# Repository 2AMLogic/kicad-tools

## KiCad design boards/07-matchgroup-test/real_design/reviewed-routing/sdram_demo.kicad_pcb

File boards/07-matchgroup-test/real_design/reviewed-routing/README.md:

# Reviewed physical routing

`sdram_demo.kicad_pcb` is the explicit routing/length-tuning artifact for the
43-part, 216-binding real SDRAM circuit. `manifest.json` binds its SHA-256 and
the exact authored source manifest. It includes the completed copper and
operator silkscreen; it is not a generic autorouter cache entry.

Run `../build.py OUTPUT` through `uv run python` to regenerate the independent
electrical source and repeat every design gate. A new logical circuit, physical
package placement or source-rule manifest requires a new reviewed routing
artifact and fresh validation; updating a hash alone is not a design review.

The build intentionally distinguishes design validation from manufacturing
export. The final order package must be generated afterward and its manifest
must pass before manufacturing readiness is claimed. Hardware has not yet been
tested.

## Class-clearance repair (Issue #6396)

The reviewed copper was first validated against the 0.15 mm native floor only.
Once #6390 declared the board's own 0.175 mm `AUX`/`SDRAM_*` classes, 42
track-to-via/pad gaps fell 0.2–25 µm short. `../repair_class_clearance_6396.py`
is the complete record of the fix. It moves 24 vias by 10–47 µm, re-attaches
their stubs at 0/45/90°, and moves one GND escape by 7 µm, then re-pins both
manifests. No class value changed. Run it with `--verify-from-git 810f833f` to
reproduce both committed PCBs byte for byte from the pre-repair artifacts.

## Evidence refresh (Issue #6404)

`build.py` fills the planes under the published router net classes, the same
`.kicad_pro`/`.kicad_dru` that sit beside the routed board. Before this, the
fills used the fab floor alone, and the saved fills failed native DRC without
`--refill-zones`. The files under `evidence/` come from that build of the
repaired copper. `scripts/boards/refresh_bundles_6404.py` regenerates them,
the routed board's fills and the manufacturing bundle together.

## Same-net copper-gap repair (Issue #9091)

Once #8938 graded same-net `physical_copper_gap` findings as errors, the
reviewed copper had 25 same-net slits: nine vias 0.07–0.12 mm from their own
pads, and narrow same-net wedges at U2.50 (DQ13), U2.39 (UDQM) and U2.53
(DQ15). `../repair_copper_gap_9091.py` is the complete record of the fix.
- It moves the nine vias 53–87 µm clear of their pads.
- It replaces a +5V staircase beside C26 with a plain T, which frees one of
  those vias.
- At DQ13 and UDQM, it removes the loops. Each trunk ran through its own pad
  and doubled back along the pad's escape, so the loop counted about 10 mm of
  length the signal never travelled. The script restores that length with
  `SerpentineGenerator` trombones on the trunks.
- It turns DQ15's shallow staircase join into a right angle and puts the
  1.5 mm it removes back into DQ15's existing meander.

Every `SDRAM_BYTE1` length is unchanged to 1 µm. DQ7 gains 0.145 mm. Run the
script with `--verify-from-git 89c2ee058` to reproduce both PCBs byte for byte.

The files under `evidence/` now describe the adopted #8603 copper (see the
section below); `refill-stability.json` and the published `../../output/`
release still describe the copper as it was before the November 2026 prune
(95c4c7eaf), until #8604's evidence refresh re-issues them.

## SDRAM_BYTE0 same-net loops (Issue #9118)

DQ7 (U2.13) and LDQM (U1.141) had the byte-1 defect from #9091: each trunk ran
through its own pad and on past it, and the authored escape doubled back along
the trunk. That is 6–7 mm of copper per net the signal never travels, but
`validate.py` sums it as matched length. Measured as the shortest path through
the copper, the real byte-0 spread was 7.51 mm against `group_skew_mm` 5.0 as
filed (the board-local model #9118 was filed with; removed by #9176). The
shared contact model, `TraceLengthAnalyzer.measure_net_path`, reads 8.16 mm on
the same stripped copper. `../repair_byte0_loops_9118.py` is the complete
record of the fix.
- It removes the loop copper, so each trunk ends inside its own pad.
- It restores the length as real series length: two `SerpentineGenerator`
  trombones, 5.93 mm on DQ7 and 6.98 mm on LDQM, on free F.Cu.
- It changes no tolerance and not `authored-source`, which never held the loops
  in this form. Only this directory's manifest is re-pinned.

Physical byte-0 spread is now 1.18 mm through `TraceLengthAnalyzer
.measure_net_path` (canonical since #9176: DQ5 62.20 to DQ2 63.37 mm; the
removed board-local model read 0.92 mm). Run the script with
`--verify-from-git c694302cd` to reproduce the PCB byte for byte, and print
the per-net lengths by measuring each with `measure_net_path` the way
`tests/test_board07_byte0_physical_spread.py` pins them.

`build.py` still reaches the same end state as after #9091: 0 native DRC
violations, 0 unconnected items, clean label and copper LVS, and only its full
`kct check` gate failing on `mask_to_copper` (#8858). `../../output/` is
therefore not re-issued here.

## Six-layer warning-free re-issue (Issue #8603)

After the November 2026 prune the reviewed copper still failed the full
`kct check` gate with 210 warnings (163 `redundant_copper_fragments`, 30
covered tracks, 14 detours and 3 silk findings), all traced to 0.05 mm
optimizer staircases that `kct pcb prune` cannot collapse. The #8603
operator ruling (option 2, 2026-11-10) authorized re-optimizing the
reviewed copper instead of accepting them.

`../engineering/retune_8603.py` optimizes the release build against the
board's own generated `.kicad_pro`/`.kicad_dru` (JLCPCB six-layer profile),
retunes the four match groups and re-derives the 14 pad-to-via authored
escapes. `../engineering/cleanup_8603.py` then simplifies the remaining
sub-0.1 mm fragment runs between their original terminals, removes covered
tracks, adds 21 same-net layer-handoff vias and stages the assembly
artwork. Both scripts refuse any input whose SHA-256 differs from the
recorded digest, and the recipe reproduces both committed PCBs byte for
byte from Git inputs:

```sh
KCT_KICAD_DOCKER=1 uv run python boards/07-matchgroup-test/real_design/engineering/cleanup_8603.py OUT
```

`sdram_demo.kicad_pcb` here is
`45943c244519945ee5d51c4b58a28a901cf67b092129c64dcd2ea90a11d2bc84` and the
authored source is
`ebff1f52709d4cb1a56d6b1558ca1051c223b746c37825ecd93c38ea81bc7575`
(`reviewed_on` 2026-11-22; the authored manifest also declares the six
board-only fiducial marks that `../build.py` and `../build_source.py` now
verify). The full gate this build repeats reports 0 errors and 0 warnings:
every `redundant_copper_*` class is 0, native DRC and ERC report no
violations, both LVS checks bind all 216 pads, the byte-0 / byte-1 /
address / command spreads are 1.952 / 4.605 / 3.648 / 4.027 mm against the
5.0 mm limit, the largest clock-relative difference is 9.881 mm and the
smallest non-pad clock gap is 0.560 mm against the 0.54 mm screen.

The redundant-copper census above runs
on the validated artifact with the board's generated `.kicad_pro` net
classes beside it. Checking the raw committed file without that project
context instead flags five candidate staircases (BOOT0, DQ1 and three
more) whose one-bend shortcuts would violate the 0.175 mm class
clearances, so the gate context is the authoritative one.

## Manufacturing recheck (Issue #8604)

The independent review on 2026-11-22 repeated the build and validator from
the post-merge inputs. Both SHA-256 values above still match the reviewed and
authored PCBs. The saved, filled production PCB is
`716d270e82df33950d7bc65c27aecc02cd4932ca9c6112429361a13db21791fb`.
Two independent builds produced this digest. At the first refill, KiCad
adds two hidden fabrication fields to each fiducial. The validator retains
all 2,869 reviewed identifiers and assigns reproducible identifiers to
those 12 fields before repeating the native save.
Pinned KiCad 10.0.6 found zero violations and opens on the saved copper and
after a separate refill. Both LVS checks bound all 216 pads. The 38 timed
nets passed their group, clock-relative and load limits. See the
[group measurements](../README.md) and [clock spacing](evidence/clock-spacing.json).

The order package uses the same filled PCB and the production DRU for both
plots and checks. Its assembly CSV contains all 43 placements. The six
board-only fiducials are present in the fabrication artwork. Hardware
testing remains pending.

## Reviewed class widths (Issue #10451)

`kct check`'s `netclass_agreement` rule (#10139) landed after this evidence
was pinned. It compares each routed net's sidecar class and `trace_width`
with the class the sibling project resolves for that net. On this board it
reported 55 `netclass_sidecar_mismatch` warnings: the six router classes in
the routed project inherited the 0.160 mm `track_width` of `Default`
(`apply_router_netclasses` clones `Default` and overrides only the name and
clearance), while `net_class_map.json` declared 0.180 mm for the 39 SDRAM
and `SWD_CLOCK` nets and 0.200 mm for the 16 `AUX` nets. `build.py` requires
zero warnings, so the replay stopped at its own design gate (#10447).

The reviewed widths are now declared in the maintained source, where they
resolve before the first zone fill. `authored-source/sdram_demo.kicad_pro`
gives `Default` the reviewed 0.180 mm that every declared class inherits, and
`authored-source/net_class_map.json` declares `AUX` at 0.180 mm. No copper
changed.

**AUX width, 0.180 mm.** The class holds the sixteen non-SDRAM nets: the
`+5V`, `+3V3` and `+3V3_A` supplies, `GND`, the `VCAP1`/`VCAP2` capacitor
links, reset, boot, debug, UART and the LED nets. On the reviewed routing,
229 of 252 `AUX` segments are 0.180 mm. That includes every supply and ground
segment and is the width the authored power routing and package escapes
carry. The other 23 segments, on `BOOT0`, `NRST`, `SWO`, `UART_TX`,
`UART_RX`, `LED_PASS_A` and `LED_FAIL_A`, are 0.200 mm. The class width is a
minimum, so those stay legal. No `AUX` net is impedance-controlled or
length-matched. IPC-2221 screening with the board's own stackup
(`kicad_tools.physics.ampacity`) needs 0.040 mm for the 230 mA bench
envelope on the 35 µm outer copper, where a 0.180 mm track screens near
0.69 A at a 10 °C rise; the inner-layer `AUX` copper carries only the
filtered analog supply and signal currents. Declaring 0.200 mm would have
reported the 229 reviewed segments as narrow and required re-routing supply
and ground to satisfy a width the copper never carried.

**Pad escapes.** No pad escape narrows below its class. Every reviewed
escape carries its class width, none of the 55 sidecar entries declares a
`neck_trace_width`, and the rule's track-width arm reports nothing on this
copper. A trunk segment narrowed below its class does fail it, and
`tests/test_board07_real_design.py` checks both.

**The two writes.** `validate.py` writes the rules once before the first
zone fill (`write_reviewed_rules`) and `kct check --emit-drc-constraints`
writes them again after the copper measurements. `class_width_errors`
resolves the written project against the sidecar after the first write and
names each drifting net before any native step runs. The validator still
requires both native sidecars to be byte-identical across the second.

**Published files.** `output/matchgroup_test_routed.kicad_pro` is the
authored project with `write_reviewed_rules` applied to the published routed
PCB. It is byte-identical to what `build.py` checks and publishes:
`50360572adf6d64ea127da337dccb79a0c9758a428070fa6c69ab73698e6c44c`.
`declare_router_netclasses_6390.py` alone re-declares the classes on
whatever `Default` width the old routed project carried, so it does not
refresh this file. The routed `.kicad_dru`
(`51c411e4dbbb48d70364da6ada60a327b4c61ad718c503b5db7503836919d2b3`) and
the saved, filled routed PCB
(`716d270e82df33950d7bc65c27aecc02cd4932ca9c6112429361a13db21791fb`) are
unchanged. The re-pinned source digests are `net_class_map.json`
`a362225403d2962e7da424ab289a285ac62d417538f4ed05167f9c55e12c224f` and
`sdram_demo.kicad_pro`
`b912b224a3f36a5ff763a9f61f79581572294f1b980bab036d2b6740af51886c`; both
PCBs above are unchanged.

The regenerated schematic carries the instance `Datasheet` the generator
now writes from each symbol definition instead of `~` (#10385); all 46
placed instances changed. `output/matchgroup_test.kicad_sch` and
`output/readiness/checked.kicad_sch` are byte-identical:
`802a7c20582e120f30878c6ae2f1f119243eaa60158da64f1bddbf544204b185`.

**Re-pin.** `scripts/boards/refresh_bundles_6404.py` rebuilt the design from
a fresh build directory and republished the evidence on the pinned
toolchain: `kicad-cli` 10.0.6 through CI's image, the synced 3D model subset
for the renders. The full `kct check` reports 0 errors and 0 warnings, the
saved and the refilled fills are byte-identical with 0 native violations and
0 unconnected items, label and copper LVS are clean, and the receipt is
`ready`. A repeat publish and a dry run from another fresh build directory,
each with the receipt's own timestamp, list 0 files.

**Package.** The re-pinned `cpl_jlcpcb.csv` differs from the previous package
in one cell: `U3` (`AP2112K-3.3TRG1`, LCSC C51118) now exports at 270°, the
catalog correction the shipped JLCPCB table gives that part on SOT-23-5
(issue #10198). The committed CPL predated it at the 180° SOT-23 default.
The bundle driver accepts only coordinate-frame changes from a fresh export,
so the corrected row was written into the committed CPL before the re-pin
and `kct export` then reproduced it byte for byte. No placement moved.

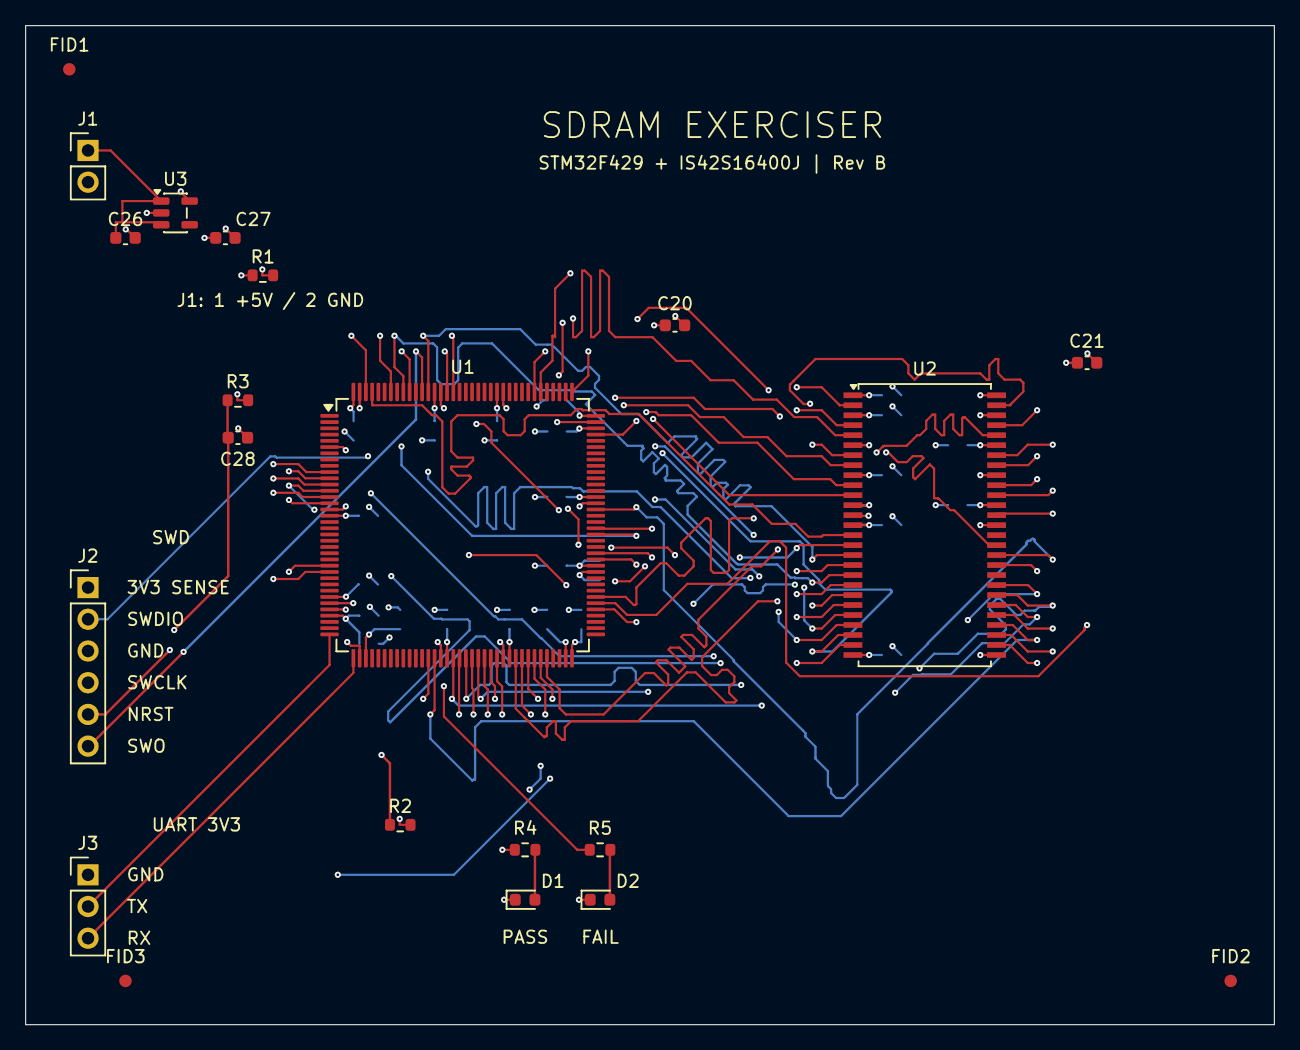
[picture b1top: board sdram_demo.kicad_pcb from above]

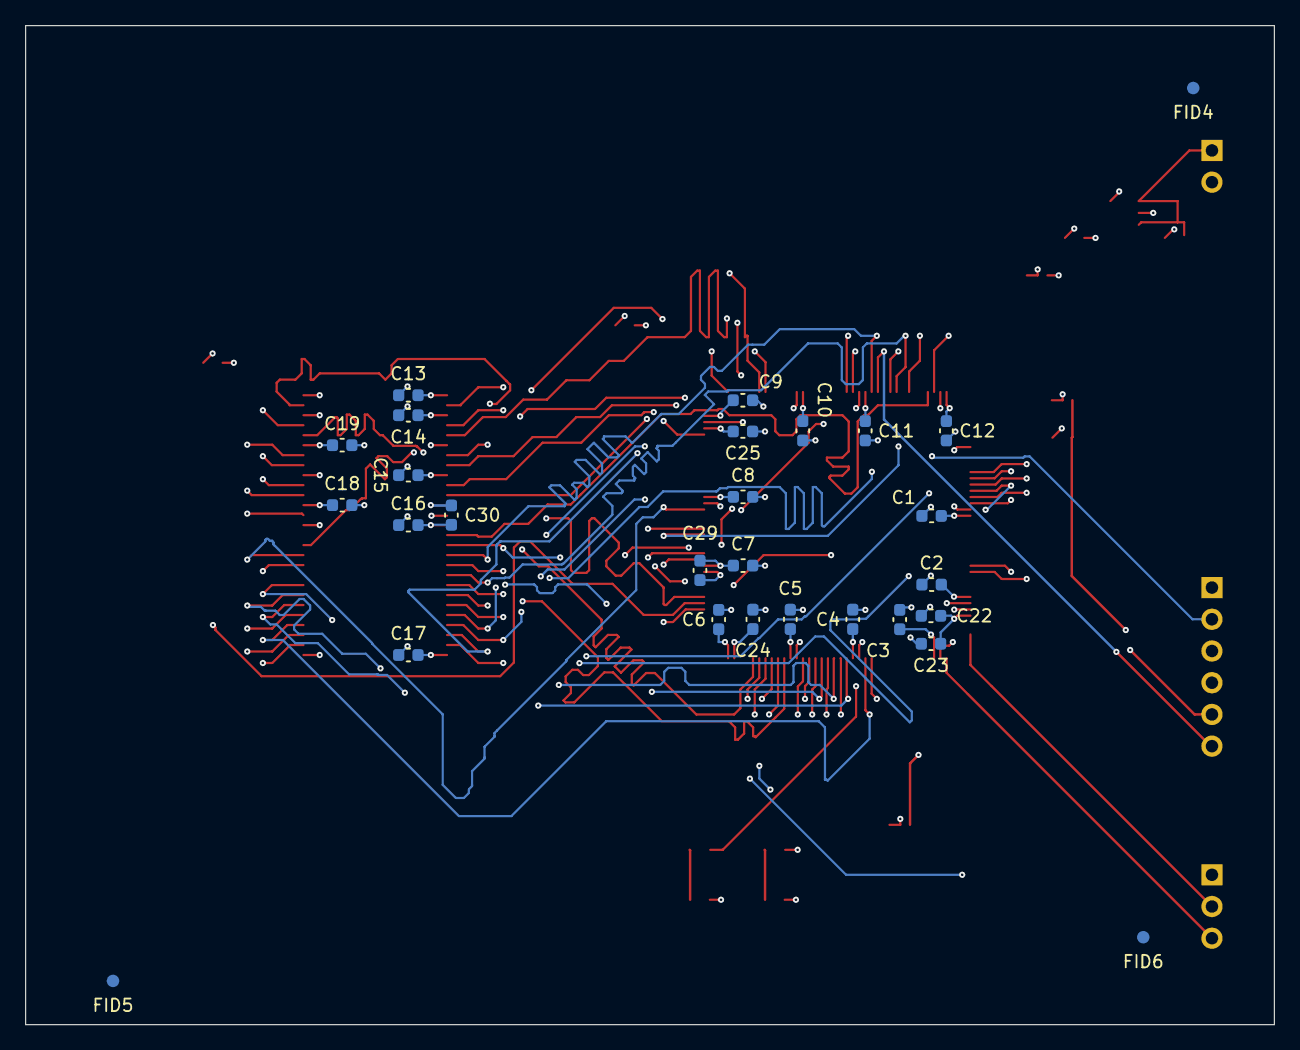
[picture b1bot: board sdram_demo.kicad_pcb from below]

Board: 6 copper layers, 100.0 x 80.0 mm, 49 parts (28 on the bottom side), 55 nets.

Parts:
C1, C2, C3, C4, C5, C6, C7, C8, C9, C10, C11, C12, C13, C14, C15, C16, C17, C18, C19, C22, C28: 100nF; C_0603_1608Metric
C20, C21: 4.7uF; C_0603_1608Metric
C23: 1uF; C_0603_1608Metric
C24, C25: 2.2uF; C_0603_1608Metric
C26, C27: 10uF; C_0603_1608Metric
C29, C30: 10nF; C_0603_1608Metric
D1: GREEN; LED_0603_1608Metric
D2: RED; LED_0603_1608Metric
FID1, FID2, FID3, FID4, FID5, FID6: Fiducial; Fiducial_1mm_Mask2mm
J1: 5V_INPUT; PinHeader_1x02_P2.54mm_Vertical
J2: SWD_3V3; PinHeader_1x06_P2.54mm_Vertical
J3: UART_3V3; PinHeader_1x03_P2.54mm_Vertical
R1: 0R; R_0603_1608Metric
R2, R3: 10k; R_0603_1608Metric
R4, R5: 1k; R_0603_1608Metric
U1: STM32F429ZIT6; LQFP-144_20x20mm_P0.5mm
U2: IS42S16400J-6TLI-TR; TSOP-II-54_22.2x10.16mm_P0.8mm
U3: AP2112K-3.3TRG1; SOT-23-5

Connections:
+3V3: C1.1, C2.1, C3.1, C4.1, C5.1, C6.1, C7.1, C8.1, C9.1, C10.1, C11.1, C12.1, C13.1, C14.1, C15.1, C16.1, C17.1, C18.1, C19.1, C20.1, C21.1, C27.1, C29.1, C30.1, J2.1, R1.1, R3.2, U1.6 (VBAT), U1.17 (VDD), U1.30 (VDD), U1.39 (VDD), U1.52 (VDD), U1.62 (VDD), U1.72 (VDD), U1.84 (VDD), U1.95 (VDD), U1.108 (VDD), U1.121 (VDD), U1.131 (VDD), U1.143 (PDR_ON), U1.144 (VDD), U2.1 (VDD), U2.3 (VDDQ), U2.9 (VDDQ), U2.14 (VDD), U2.27 (VDD), U2.43 (VDDQ), U2.49 (VDDQ), U3.5 (VOUT)
+3V3_A: C22.1, C23.1, R1.2, U1.32 (VREF+), U1.33 (VDDA)
+5V: C26.1, J1.1, U3.1 (VIN), U3.3 (EN)
A0: U1.10 (PF0), U2.23 (A0)
A1: U1.11 (PF1), U2.24 (A1)
A2: U1.12 (PF2), U2.25 (A2)
A3: U1.13 (PF3), U2.26 (A3)
A4: U1.14 (PF4), U2.29 (A4)
A5: U1.15 (PF5), U2.30 (A5)
A6: U1.50 (PF12), U2.31 (A6)
A7: U1.53 (PF13), U2.32 (A7)
A8: U1.54 (PF14), U2.33 (A8)
A9: U1.55 (PF15), U2.34 (A9)
A10: U1.56 (PG0), U2.22 (A10)
A11: U1.57 (PG1), U2.35 (A11)
BA0: U1.89 (PG4), U2.20 (BA0)
BA1: U1.90 (PG5), U2.21 (BA1)
BOOT0: R2.1, U1.138 (BOOT0)
DQ0: U1.85 (PD14), U2.2 (DQ0)
DQ1: U1.86 (PD15), U2.4 (DQ1)
DQ2: U1.114 (PD0), U2.5 (DQ2)
DQ3: U1.115 (PD1), U2.7 (DQ3)
DQ4: U1.58 (PE7), U2.8 (DQ4)
DQ5: U1.59 (PE8), U2.10 (DQ5)
DQ6: U1.60 (PE9), U2.11 (DQ6)
DQ7: U1.63 (PE10), U2.13 (DQ7)
DQ8: U1.64 (PE11), U2.42 (DQ8)
DQ9: U1.65 (PE12), U2.44 (DQ9)
DQ10: U1.66 (PE13), U2.45 (DQ10)
DQ11: U1.67 (PE14), U2.47 (DQ11)
DQ12: U1.68 (PE15), U2.48 (DQ12)
DQ13: U1.77 (PD8), U2.50 (DQ13)
DQ14: U1.78 (PD9), U2.51 (DQ14)
DQ15: U1.79 (PD10), U2.53 (DQ15)
GND: C1.2, C2.2, C3.2, C4.2, C5.2, C6.2, C7.2, C8.2, C9.2, C10.2, C11.2, C12.2, C13.2, C14.2, C15.2, C16.2, C17.2, C18.2, C19.2, C20.2, C21.2, C22.2, C23.2, C24.2, C25.2, C26.2, C27.2, C28.2, C29.2, C30.2, D1.1 (K), D2.1 (K), J1.2, J2.3, J3.1, R2.2, U1.16 (VSS), U1.31 (VSSA), U1.38 (VSS), U1.51 (VSS), U1.61 (VSS), U1.83 (VSS), U1.94 (VSS), U1.107 (VSS), U1.120 (VSS), U1.130 (VSS), U2.6 (GNDQ), U2.12 (GNDQ), U2.28 (GND), U2.41 (GND), U2.46 (GNDQ), U2.52 (GNDQ), U2.54 (GND), U3.2 (GND)
LDQM: U1.141 (PE0), U2.15 (LDQM)
LED_FAIL: R5.1, U1.129 (PG14)
LED_FAIL_A: D2.2 (A), R5.2
LED_PASS: R4.1, U1.128 (PG13)
LED_PASS_A: D1.2 (A), R4.2
NRST: C28.1, J2.5, R3.1, U1.25 (NRST)
SDCKE1: U1.135 (PB5), U2.37 (CKE)
SDCLK: U1.93 (PG8), U2.38 (CLK)
SDNCAS: U1.132 (PG15), U2.17 (~CAS)
SDNE1: U1.136 (PB6), U2.19 (~CS)
SDNRAS: U1.49 (PF11), U2.18 (~RAS)
SDNWE: U1.26 (PC0), U2.16 (~WE)
SWCLK: J2.4, U1.109 (PA14)
SWDIO: J2.2, U1.105 (PA13)
SWO: J2.6, U1.133 (PB3)
UART_RX: J3.3, U1.37 (PA3)
UART_TX: J3.2, U1.36 (PA2)
UDQM: U1.142 (PE1), U2.39 (UDQM)
VCAP1: C24.1, U1.71 (VCAP_1)
VCAP2: C25.1, U1.106 (VCAP_2)

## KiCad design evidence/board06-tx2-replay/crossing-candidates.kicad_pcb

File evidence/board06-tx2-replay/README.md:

# Board 06 TX2 relief replay

Issues #9936 and #10032 use this reduced test case. It restores the saved copper, negotiated usage and congestion history from an earlier iteration-two relief capture on Board 06. Its input PCB has the same SHA-256 as the input to the complete seed-42 run. The captured occupancy predates that run. The routing source for this replay is `efafdb1f4c2d16743fec94b1e96f0b458e81b76a`. [Full run and both saved boards](https://github.com/2AMLogic/kicad-tools/actions/runs/45017437753) · [Historical capture context](https://github.com/2AMLogic/kicad-tools/pull/9915#issuecomment-7078414198)

From the root of this checkout, run the following commands. Each output directory must be new.

```sh
uv sync --frozen --extra dev
uv run kct build-native
uv run kct build-native --check
PYTHONHASHSEED=42 uv run python evidence/board06-tx2-replay/replay.py python /tmp/tx2-positive-first
PYTHONHASHSEED=42 uv run python evidence/board06-tx2-replay/replay.py python /tmp/tx2-negative-first --negative-first
PYTHONHASHSEED=42 uv run python evidence/board06-tx2-replay/replay.py cpp /tmp/tx2-cpp
```

The first transaction connects its target. The second reaches the opposite pad pair, displaces the first route and fails to reconnect it. The nested attempt encounters the reciprocal failure. The saved output keeps the first net and contains zero added or removed tracks or vias relative to the preceding saved board. Reversing the order exchanges which net survives. The Python runs hit two 120-second deadlines. C++ reached its million-expansion limit in the reduced case. The complete C++ run connected all 21 benchmark signals.

`results.json` names both the outer transaction and the net actually being searched. Each run writes the starting board and both post-transaction PCBs with their matching project and design-rule sidecars. The checkpoint uses JSON, and the numeric NumPy archive loads with `allow_pickle=False`.

## Post-#9936 measurements

The #9936 work re-ran this replay on top of the fix commit and measured the failing re-land search directly (all on the identical restored grid state, before any copper is placed; the intercept harness drove the same two-transaction order through production `_relief_rescue`):

| Search of displaced `USB3_TX2+` (`J1.B2->U2.F2`, partner route committed) | Outcome |
| --- | --- |
| Forward, unbiased, 120 s backstop | deadline hit at 277,504–290,816 of 1,000,000 expansions (cut short) |
| Forward, goal-bias weight 1.5 (#9901 extension) | deadline hit — same outcome as unbiased |
| Forward, weights 2.0 and 3.0 | deadline hit at 380,928 / 303,104 expansions |
| Forward, unbiased, 600 s | stopped at ~534 s by the 1,000,000-expansion cap (iteration-limited, not a drain; an uncapped rerun was still expanding well past that count) |
| Reverse pad order, unbiased | **frontier drained in 0.9 s (`last_route_exhausted` = proof)** |

A drained open set is the pathfinder's unreachability proof (#6098), and unreachability is direction-independent — so the 0.9 s reverse drain proves the displaced partner has **no normal-sharing-mode path once the Python rescue's own `USB3_TX2-` route is committed** (the forward direction simply cannot afford the drain: its reachable component needs more than the 1,000,000-expansion cap to exhaust). The 120-second backstop was reporting this proof as a cut-short deadline. With the #9936 instrumentation the production rollback log now states the measured exit per victim, for example:

```
Relief rescue: USB3_TX2- re-land failure exits (issue #9936): USB3_TX2+ -- J1.B2->U2.F2: wall deadline hit at 290816 expansions (search cut short)
```

The C++ replay of the same transaction (also re-run on top of the fix) stops at its 1,000,000-expansion iteration cap instead of the wall backstop, and its structured diagnostics name the closing copper: the exit line reports `iteration cap reached at 1,000,000 expansions (search cut short); last blocker USB3_RX2+ at (118.0, 55.5)` for the TX2+ re-land and the symmetric `USB3_RX2- at (117.0, 55.5)` blocker for the reciprocal TX2− re-land inside the nested rescue. Both backends restore the board exactly (zero added or removed tracks and vias).

The saved boards were re-checked with the pinned evidence toolchain (KiCad 10.0.6 through CI's image, scratch `KICAD_CONFIG_HOME`, each board with its matching `.kicad_pro` / `.kicad_dru`): `jointly-connected.kicad_pcb` has 0 DRC errors and 0 opens on the TX2 nets (the feasible control); both post-transaction rollback boards (`after-2` of the Python and C++ replays) have 0 DRC errors and exactly the pre-attempt connectivity — 1 open on USB3_TX2−, TX2+ connected, 156 unrelated opens inherited from the fixture (the constrained control).

The jointly-connected control below demonstrates the captured copper admits a coexisting pair — but with the C++ routes. The measured limitation handed to #9850: the sequential Python rescue commits the first conflict-free probe path for the rescued leg, that route's halo seals the displaced partner's re-land (proved), the depth-1 nested rescue only swaps which leg is sealed, and the transaction correctly rolls back verbatim (zero added or removed tracks and vias). Repairing reach requires choosing the rescued leg's route under the partner's re-land constraint (coupled re-landing), which this issue leaves to the parent.

## Physical controls

Both controls retain the captured neighbor copper. The routed profile files are byte-identical across both backends in the complete run. For a native check, copy the PCB and its matching sidecars into a new directory under one basename, then run KiCad 10.0.6 with the project's pinned configuration.

| PCB | TX2+ and TX2− pad islands | Native opens on the two nets | Native DRC errors |
| --- | --- | --- | --- |
| `jointly-connected.kicad_pcb` | One each | Zero each | 0 |
| `crossing-candidates.kicad_pcb` | One each | Zero each | 9 |

The first control adds the two actual TX2 routes from the complete C++ board. TX2+ uses 66 front-copper segments and TX2− uses nine, all 0.275 mm wide, with no vias. The second combines Python's two independently successful routes. KiCad finds five shorts, one crossing, two clearance errors and one differential-pair gap error. These partially routed controls have 156 opens on other nets and six footprint-library warnings. The first control demonstrates that both nets can coexist with this captured neighbor copper. The four outer failures in the complete Python run have different occupancy and victim counts.

## Partner drill clearance on the Python replay (#10032)

The first TX2− probe selects a BGA via at (151.75, 70.35) mm. This leaves 0.0500 mm between its drill and the displaced TX2+ drill at (151.45, 70.35) mm. The project requires 0.5000 mm. The Python relief transaction tries a normal route from U2.F3 to J1.B3 with the original TX2+ drill sites reserved. This extra search has a 4,096-expansion ceiling and honors a smaller existing cap. On this capture the frontier drained in 0.28 s. The ordinary rescue then found a TX2− path, failed to reconnect TX2+, and restored every track, via and pad island. TX2+ remained connected and TX2− remained open.

An independent reverse search on the captured neighbors, with the other leg absent, excludes each BGA-side via it finds before trying again. Both legs exhausted their frontiers after two sites. All dimensions below are in millimeters. The two 0.25 mm drills leave their center distance minus 0.25 mm between hole edges.

| TX2+ site | TX2− site | Hole gap |
| --- | --- | ---: |
| (151.45, 69.70) | (151.75, 69.70) | 0.0500 |
| (151.45, 69.70) | (151.75, 70.35) | 0.4659 |
| (151.45, 70.35) | (151.75, 69.70) | 0.4659 |
| (151.45, 70.35) | (151.75, 70.35) | 0.0500 |

`partner-candidate.json` contains the original connected TX2+ and a Python TX2− candidate found while reserving space around that positive path. Its segment records store (x1, y1, x2, y2, layer, width), and its via records store (x, y, first layer, last layer, diameter, drill). Both routes use the captured neighbors. The second control moves only the TX2− via from (151.75, 69.70) to (151.75, 69.65) and joins the old center to the new one on F.Cu and In1.Cu inside the via land. This yields 0.5116 mm of hole clearance. The original Python grid rejects the moved via. Its via-clearance footprint reaches the F.Cu cell at (151.80, 69.20), which `_apply_stitch_via_halo` reserved when registering U2.E3 (+1V2). That reservation preserves space to stitch a plane-net pad. The C++ physical control instead uses front copper throughout both legs.

| Saved PCB | TX2+ / TX2− pad islands | Native TX2 opens | Native errors | Native warnings |
| --- | --- | --- | ---: | ---: |
| Before and after the failed rescue | 1 / 2 | One on TX2− | 0 | 11 |
| Recorded candidate, opposite drill rows | 1 / 1 | Zero | 0 | 12, including `hole_to_hole` |
| One-cell physical control | 1 / 1 | Zero | 0 | 11 |
| Existing C++ joint control | 1 / 1 | Zero | 0 | 11 |

The 11 shared warnings concern silkscreen and text. All boards have 156 unrelated opens. These partial-board measurements apply to the captured occupancy. [Full-board comparison and remaining four negative legs](https://github.com/2AMLogic/kicad-tools/issues/9850)

From the repository root, use new output paths. The native checker regenerates the seven fixture footprints from Board 06’s generator, installs them in a scratch project, and runs pinned KiCad 10.0.6 with the board’s routed project and rule files. It refuses a library-environment finding.

```sh
fixture=evidence/board06-tx2-replay
PYTHONHASHSEED=42 uv run python "$fixture/replay.py" python /tmp/tx2-rescue
PYTHONHASHSEED=42 uv run python "$fixture/terminal_sites.py" /tmp/tx2-sites
uv run python "$fixture/native_check.py" /tmp/tx2-rescue/after-2.kicad_pcb /tmp/tx2-rollback.json
uv run python "$fixture/native_check.py" /tmp/tx2-sites/paired-candidate.kicad_pcb /tmp/tx2-paired.json
uv run python "$fixture/native_check.py" /tmp/tx2-sites/one-cell-control.kicad_pcb /tmp/tx2-one-cell.json
uv run python "$fixture/native_check.py" "$fixture/jointly-connected.kicad_pcb" /tmp/tx2-joint.json
```

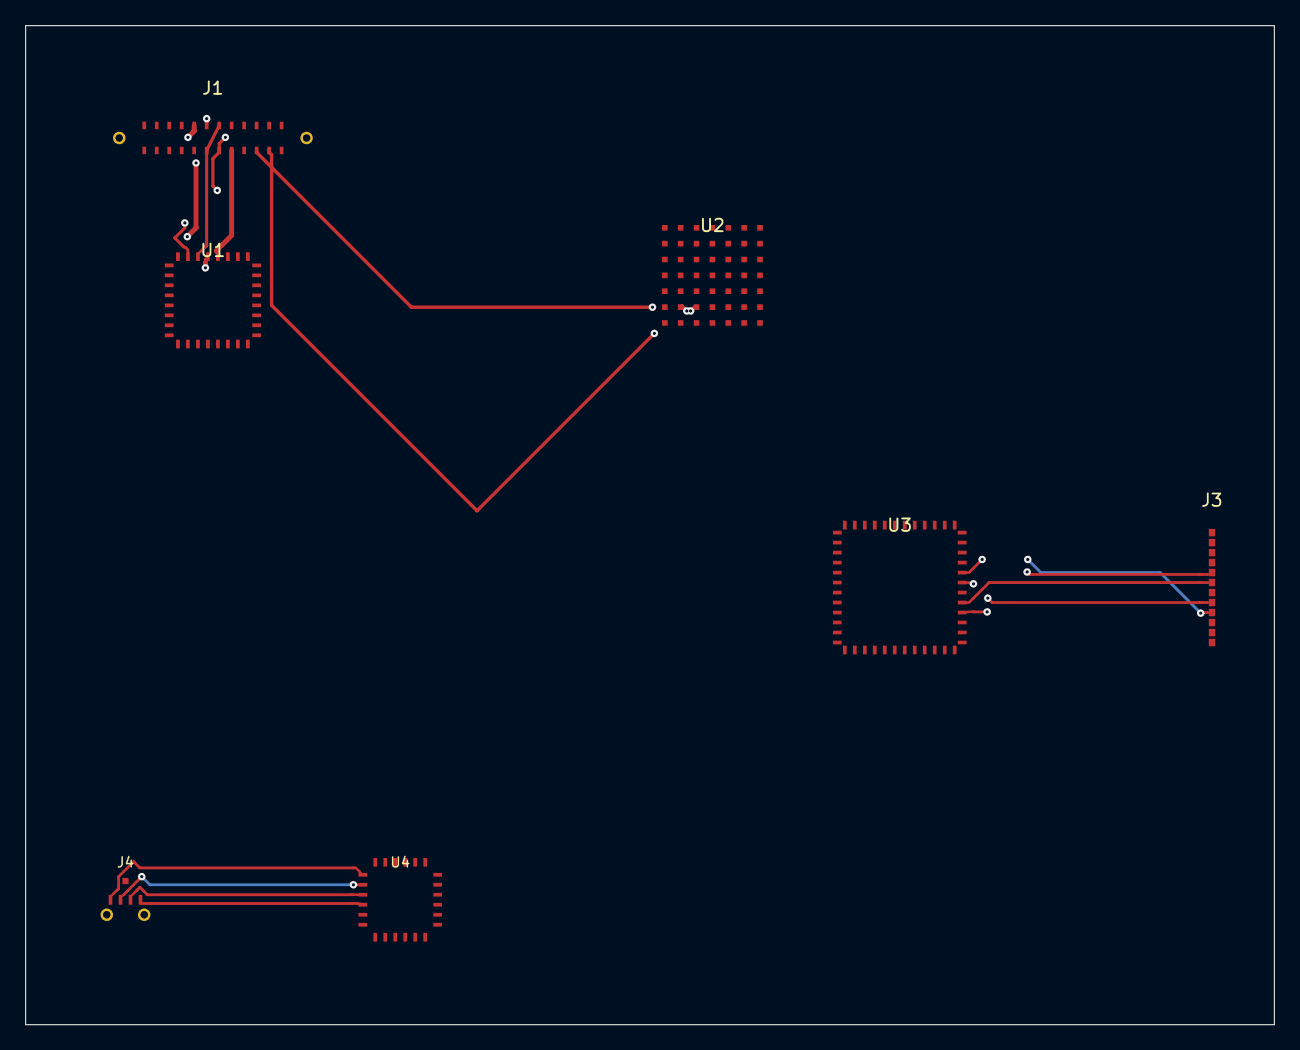
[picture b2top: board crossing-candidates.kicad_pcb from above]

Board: 4 copper layers, 100.0 x 80.0 mm, 7 parts (0 on the bottom side), 26 nets.

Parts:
J1: USB-C; USB_C_Receptacle_USB2.0
J3: MiniPCIe; PCIE_Mini_Edge
J4: FFC4; FFC_4P_0.5mm
U1: QFN32_USB2; QFN-32-1EP_5x5mm_P0.5mm
U2: BGA49_USB3; BGA-49_5.0x5.0mm_Layout7x7_P0.5mm
U3: QFP48_PCIe; LQFP-48_7x7mm_P0.5mm
U4: QFN24_MIPI; QFN-24-1EP_4x4mm_P0.5mm

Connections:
+1V2: J3.10, U2.C3, U2.C4, U2.C5, U2.D2, U2.D3, U2.D4, U2.D5, U2.D6, U2.E3, U2.E4, U2.E5, U3.36
+1V8: U1.16, U4.6, U4.18
+3V3: J1.A8, J1.B8, J3.3, U1.1, U1.17, U2.C2, U2.C6, U2.E2, U2.E6, U3.25, U4.12
GND: J1.A1, J1.A12, J1.B1, J1.B12, J1.S1, J1.S2, J3.1, J3.2, J3.4, J3.7, J3.11, J3.12, J4.M1, J4.M2, U1.2, U1.3, U1.4, U1.5, U1.6, U1.7, U1.8, U1.14, U1.15, U1.18, U1.19, U1.20, U1.21, U1.22, U1.23, U1.24, U1.25, U1.26, U1.27, U1.28, U1.29, U1.30, U1.31, U1.32, U2.A1, U2.A2, U2.A3, U2.A4, U2.A5, U2.A6, U2.A7, U2.B1, U2.B4, U2.B7, U2.C1, U2.C7, U2.D1, U2.D7, U2.E1, U2.E7, U2.F1, U2.F4, U2.F7, U2.G1, U2.G2, U2.G3, U2.G4, U2.G5, U2.G6, U2.G7, U3.1, U3.2, U3.3, U3.4, U3.5, U3.6, U3.7, U3.8, U3.9, U3.10, U3.11, U3.12, U3.13, U3.14, U3.15, U3.16, U3.17, U3.18, U3.19, U3.20, U3.21, U3.22, U3.23, U3.24, U3.26, U3.27, U3.30, U3.33, U3.34, U3.35, U3.37, U3.38, U3.39, U3.40, U3.41, U3.42, U3.43, U3.44, U3.45, U3.46, U3.47, U3.48, U4.7, U4.8, U4.9, U4.10, U4.11, U4.13, U4.14, U4.15, U4.16, U4.17, U4.19, U4.20, U4.21, U4.22, U4.23, U4.24
MIPI_CLK+: J4.1, U4.1
MIPI_CLK-: J4.2, U4.2
MIPI_D0+: J4.3, U4.3
MIPI_D0-: J4.4, U4.4
MIPI_RST: J4.RST, U4.5
PCIE_RX+: J3.8, U3.31
PCIE_RX-: J3.9, U3.32
PCIE_TX+: J3.5, U3.28
PCIE_TX-: J3.6, U3.29
USB2_D+: J1.A6, J1.B6, U1.10
USB2_D-: J1.A7, J1.B7, U1.11
USB3_RX1+: J1.B11, U2.B5
USB3_RX1-: J1.B10, U2.B6
USB3_RX2+: J1.A11, U2.F5
USB3_RX2-: J1.A10, U2.F6
USB3_TX1+: J1.A2, U2.B2
USB3_TX1-: J1.A3, U2.B3
USB3_TX2+: J1.B2, U2.F2
USB3_TX2-: J1.B3, U2.F3
USB_CC1: J1.A5, U1.12
USB_CC2: J1.B5, U1.13
VBUS_USB: J1.A4, J1.A9, J1.B4, J1.B9, U1.9

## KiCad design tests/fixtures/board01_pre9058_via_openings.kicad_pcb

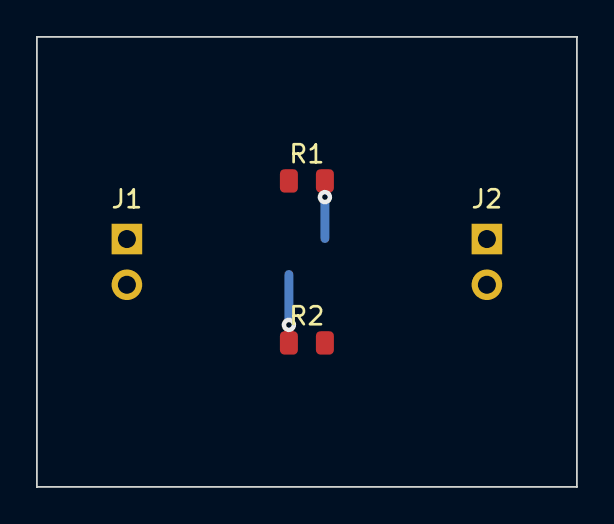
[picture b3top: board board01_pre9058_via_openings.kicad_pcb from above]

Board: 2 copper layers, 30.0 x 25.0 mm, 4 parts (0 on the bottom side), 3 nets.

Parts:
J1, J2: PinHeader_1x02_P2.54mm_Vertical
R1, R2: R_0805_2012Metric

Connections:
GND: J1.2, J2.2, R2.2
VIN: J1.1, R1.1
VOUT: J2.1, R1.2, R2.1
